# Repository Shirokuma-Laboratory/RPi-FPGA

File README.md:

# RPi-FPGA LMCXO2-100 (Now Testing)
ラティス・セミコンダクタ MachXO2 FPGA を用いた Raspberry Pi I/O 拡張モジュール  
Raspberry Pi I/O extention module using Lattice semiconductor MachXO2 FPGA.

このモジュールは、ラティス・セミコンダクタ MachXO2 FPGA の 0.5mm ピッチ TQFP 100ピン・パッケージ・デバイス 向けに設計されました。  
This module is desined for 0.5mm pitch TQFP 100pin package devices of Lattice semiconductor MachXO2 FPGAs.  
Raspberry Pi から 3.3v の供給を受け、コア電圧 3.3v のHC型デバイスが使えます。  
Since 3.3v power is supplied from Raspberry Pi, the HC type devices that has 3.3v of the core voltages can be used.  
Table 1 に、Lattice semiconductor MachXO2 FPGA シリーズの利用可能なモデルとその機能を示します。  
Table 1 shows available models and features of Lattice semiconductor MachXO2 FPGAs.  
  
Table 1: Available Models and features of Lattice semiconductor MachXO2 FPGAs.
|model|XO2-256|XO2-640|XO2-1200|XO2-2000|
|:-------:|----------:|----------:|----------:|-----------:|
|LUTs |256|640|1280|2112|
|I/Os |55|78|79|79| 
|EBR SRAM<br>(kbits)|0|18|64|74|
|Dist SRAM<br>(kbits)|2|5|10|16|
|Flash<br>(kbits)|0|24|64|80|
|PLL|0|0|1|1|

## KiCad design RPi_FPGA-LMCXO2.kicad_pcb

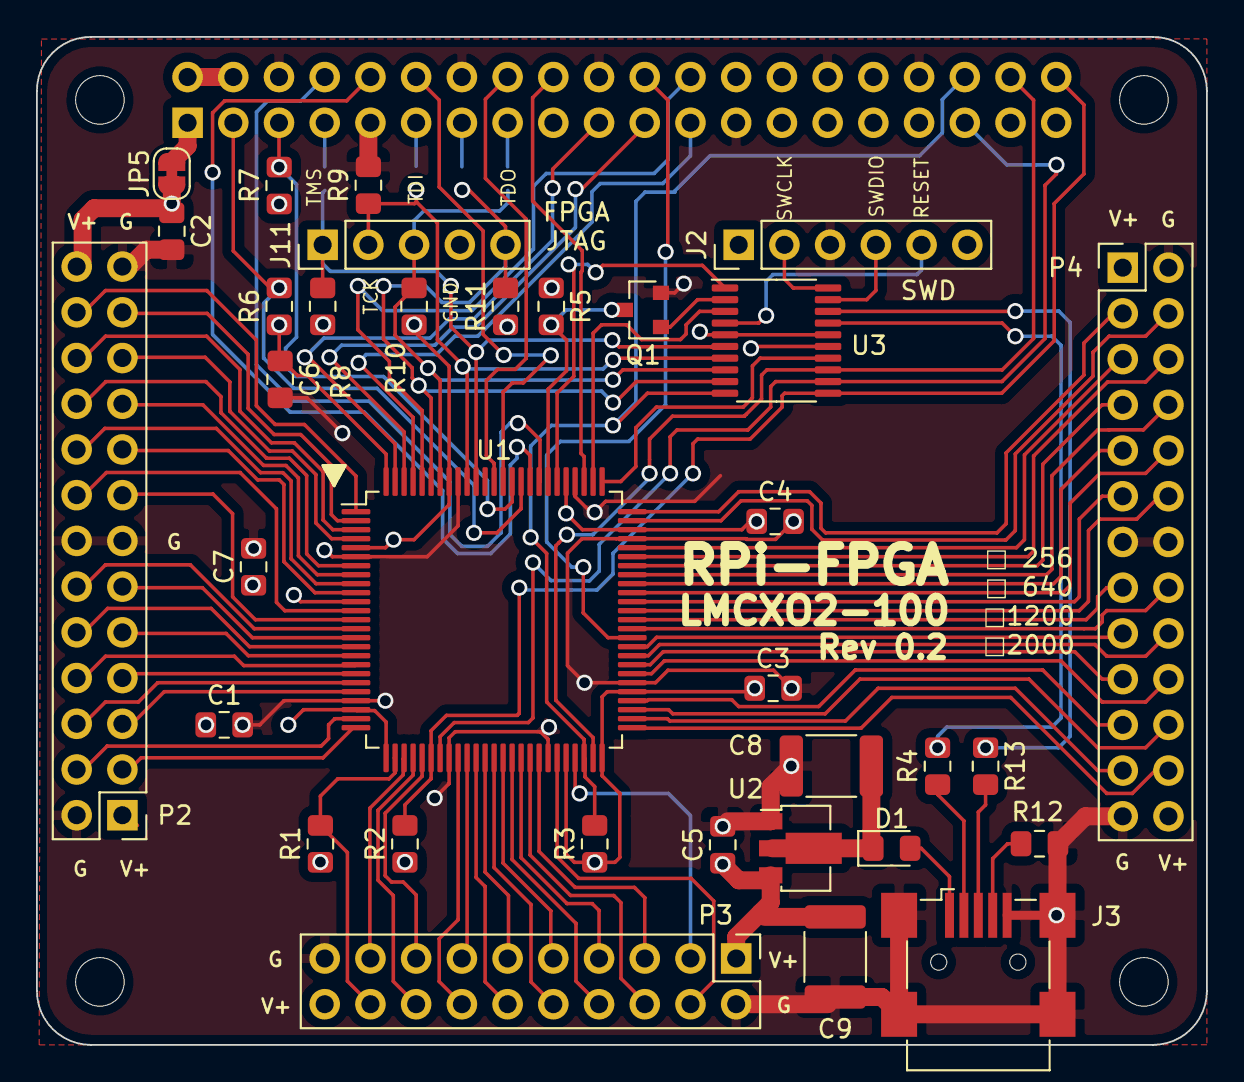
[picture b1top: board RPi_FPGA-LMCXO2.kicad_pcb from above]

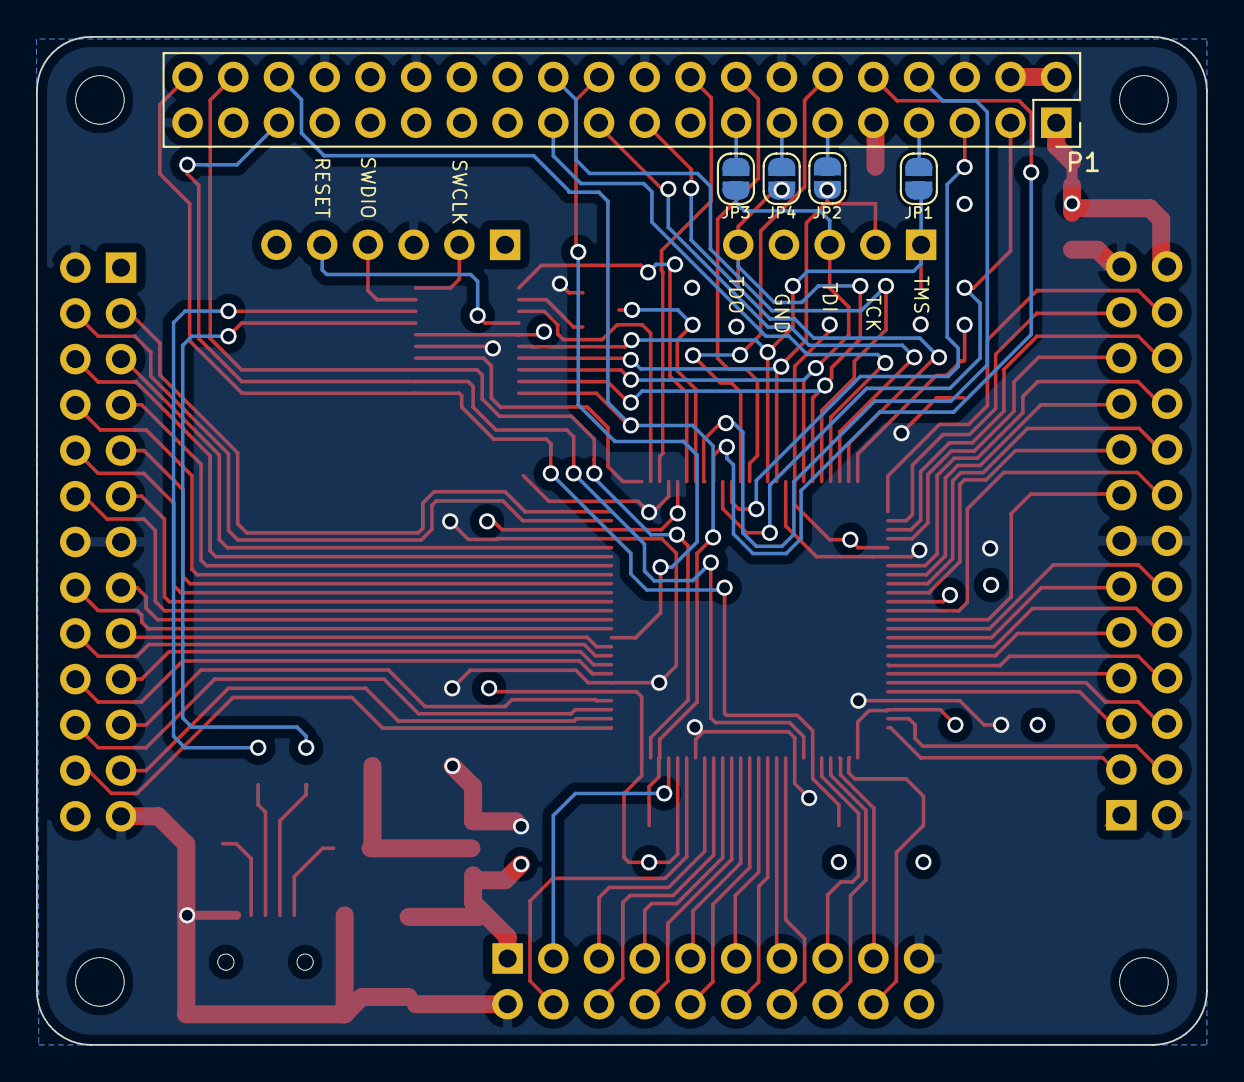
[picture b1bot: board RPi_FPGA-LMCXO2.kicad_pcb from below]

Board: 4 copper layers, 65.0 x 56.0 mm, 43 parts (5 on the bottom side), 99 nets.

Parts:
C1, C2, C3, C4, C5, C6, C7: 0.1u; C_0805_2012Metric_Pad1.15x1.40mm_HandSolder
C8, C9: 10u; C_1812_4532Metric_Pad1.30x3.40mm_HandSolder
D1: D; D_0805_2012Metric_Pad1.15x1.40mm_HandSolder
J2: SWD; PinHeader_1x06_P2.54mm_Vertical
J3: USB_B_Mini; USB_Mini-B_Wuerth_65100516121_Horizontal
J11: JTAG; PinHeader_1x05_P2.54mm_Vertical
JP1, JP2, JP3, JP4: SolderJumper_2_Open; SolderJumper-2_P1.3mm_Open_RoundedPad1.0x1.5mm
JP5: SolderJumper_2_Bridged; SolderJumper-2_P1.3mm_Bridged_RoundedPad1.0x1.5mm
MK1, MK2, MK3, MK4: M2.5; MountingHole_2.7mm_M2.5
P1: RPi-I/O; PinSocket_2x20_P2.54mm_Vertical
P2: Ext-I/O-1; PinHeader_2x13_P2.54mm_Vertical
P3: Ext_I/O-2; PinHeader_2x10_P2.54mm_Vertical
P4: Conn_02x13_Odd_Even; PinHeader_2x13_P2.54mm_Vertical
Q1: DTC144G; SOT-23
R1, R2, R3: 4K7; R_0805_2012Metric_Pad1.15x1.40mm_HandSolder
R4, R13: R; R_0805_2012Metric_Pad1.15x1.40mm_HandSolder
R5, R6, R7, R8, R9, R10, R11: 4k7; R_0805_2012Metric_Pad1.15x1.40mm_HandSolder
R12: 100k; R_0805_2012Metric_Pad1.15x1.40mm_HandSolder
U1: LMCXO2-2000-100; LQFP-100_14x14mm_P0.5mm
U2: MCP1700-3302E_SOT89; SOT-89-3
U3: STM32F042F4Px; TSSOP-20_4.4x6.5mm_P0.65mm

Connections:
+3V3: C1.1, C2.1, C3.1, C4.1, C5.1, C6.1, C7.1, C9.1, J2.1, JP5.1, P2.1, P2.26, P3.1, P3.20, P4.1, P4.26, R1.1, R2.1, R3.1, R5.1, R6.1, R7.1, R8.1, R10.1, R11.1, U1.5, U1.11, U1.23, U1.26, U1.46, U1.50, U1.55, U1.73, U1.80, U1.93, U1.100, U2.3, U3.5, U3.16
+5V: P1.2, P1.4
/GPIO2(SDA1): P1.3, R6.2, U1.85
/GPIO3(SCL1): P1.5, R7.2, U1.86
/GPIO4(GCLK): JP1.2, P1.7
/GPIO8(SPI0_CE_N): P1.24, U1.96
/GPIO9(SPI0_MISO): P1.21, U1.98
/GPIO10(SPI0_MOSI): P1.19, U1.99
/GPIO11(SPI0_SCK): P1.23, U1.97
/GPIO14(TXD0): P1.8, U1.83
/GPIO15(RXD0): P1.10, U1.84
/GPIO16: P1.36, R3.2, U1.48, U3.10
/GPIO17(GEN0): JP2.2, P1.11
/GPIO18(GEN1)(PWM0): P1.12, U1.87
/GPIO19(SPI1_MISO): P1.35, U1.32, U3.12
/GPIO20(SPI1_MOSI): P1.38, U1.49, U3.13
/GPIO21(SPI1_SCK): P1.40, R2.2, U1.31, U3.11
/GPIO22(GEN3): JP3.2, P1.15
/GPIO23(GEN4): P1.16, U1.88
/GPIO24(GEN5): P1.18, U1.78
/GPIO25(GEN6): P1.22, U1.61
/GPIO27(GEN2): JP4.2, P1.13
/LMCXO2-A/PB5A: P3.18, R1.2, U1.27
/LMCXO2-A/PB5B: P3.17, U1.28
/LMCXO2-A/PB6A: P3.16, U1.29
/LMCXO2-A/PB6B: P3.15, U1.30
/LMCXO2-A/PB11A: P3.14, U1.34
/LMCXO2-A/PB11B: P3.13, U1.35
/LMCXO2-A/PB12A: P3.12, U1.36
/LMCXO2-A/PB12B: P3.11, U1.37
/LMCXO2-A/PB16A: P3.10, U1.38
/LMCXO2-A/PB16B: P3.9, U1.39
/LMCXO2-A/PB18A: P3.8, U1.40
/LMCXO2-A/PB18B: P3.7, U1.41
/LMCXO2-A/PB21A: P3.6, U1.42
/LMCXO2-A/PB21B: P3.5, U1.43
/LMCXO2-A/PB22A: P3.4, U1.45
/LMCXO2-A/PB22B: P3.3, U1.47
/LMCXO2-A/PL2A: P2.24, U1.1
/LMCXO2-A/PL2B: P2.23, U1.2
/LMCXO2-A/PL3A: P2.22, U1.3
/LMCXO2-A/PL3B: P2.21, U1.4
/LMCXO2-A/PL4A: P2.20, U1.7
/LMCXO2-A/PL4B: P2.19, U1.8
/LMCXO2-A/PL5A: P2.18, U1.9
/LMCXO2-A/PL5B: P2.17, U1.10
/LMCXO2-A/PL7C: P2.16, U1.12
/LMCXO2-A/PL7D: P2.15, U1.13
/LMCXO2-A/PL9A: P2.12, U1.14
/LMCXO2-A/PL9B: P2.11, U1.15
/LMCXO2-A/PL10A: P2.10, U1.16
/LMCXO2-A/PL10B: P2.9, U1.17
/LMCXO2-A/PL11A: P2.8, U1.18
/LMCXO2-A/PL11B: P2.7, U1.19
/LMCXO2-A/PL12A: P2.6, U1.20
/LMCXO2-A/PL12B: P2.5, U1.21
/LMCXO2-A/PL14A: P2.4, U1.24
/LMCXO2-A/PL14B: P2.3, U1.25
/LMCXO2-B/DONE: U1.76, U3.14
/LMCXO2-B/INITN: U1.77, U3.3
/LMCXO2-B/JTAGENB: Q1.3, R5.2, U1.82
/LMCXO2-B/PR2A: P4.3, U1.75
/LMCXO2-B/PR2B: P4.4, U1.74
/LMCXO2-B/PR3A: P4.5, U1.71
/LMCXO2-B/PR3B: P4.6, U1.70
/LMCXO2-B/PR4A: P4.7, U1.69
/LMCXO2-B/PR4B: P4.8, U1.68
/LMCXO2-B/PR5A: P4.9, U1.67
/LMCXO2-B/PR5B: P4.10, U1.66
/LMCXO2-B/PR6A: P4.11, U1.65
/LMCXO2-B/PR6B: P4.12, U1.64
/LMCXO2-B/PR7A: P4.15, U1.63
/LMCXO2-B/PR7B: P4.16, U1.62
/LMCXO2-B/PR10A: P4.17, U1.60
/LMCXO2-B/PR10B: P4.18, U1.59
/LMCXO2-B/PR11A: P4.19, U1.58
/LMCXO2-B/PR11B: P4.20, U1.57
/LMCXO2-B/PR12A: P4.21, U1.54
/LMCXO2-B/PR12B: P4.22, U1.53
/LMCXO2-B/PR14A: P4.23, U1.52
/LMCXO2-B/PR14B: P4.24, U1.51
/LMCXO2-B/PRGM: U1.81, U3.1
/STM32F042F/JTAGEN: Q1.1, U3.2
/STM32F042F/RESET: J2.5, U3.4
/STM32F042F/SWCLK: J2.2, U3.20
/STM32F042F/SWDIO: J2.4, U3.19
/STM32F042F/USB_DM: R4.1, U3.17
/STM32F042F/USB_DP: R13.1, U3.18
/TCK: J11.2, JP2.1, R9.1, U1.91, U3.7
/TDI: J11.3, JP3.1, R10.2, U1.94, U3.8
/TDO: J11.5, JP4.1, R11.2, U1.95, U3.9
/TMS: J11.1, JP1.1, R8.2, U1.90, U3.6
GND: C1.2, C2.2, C3.2, C4.2, C5.2, C6.2, C7.2, C8.2, C9.2, J2.3, J3.5, J3.6, J11.4, P1.6, P1.9, P1.14, P1.20, P1.25, P1.30, P1.34, P1.39, P2.2, P2.13, P2.14, P2.25, P3.2, P3.19, P4.2, P4.13, P4.14, P4.25, Q1.2, R9.2, R12.1, U1.6, U1.22, U1.33, U1.44, U1.56, U1.72, U1.79, U1.92, U2.1, U3.15
unnamed: C8.1, D1.1, U2.2
unnamed: D1.2, J3.1
unnamed: J3.2, R4.2
unnamed: J3.3, R13.2
unnamed: J3.4, R12.2
unnamed: JP5.2, P1.1, P1.17
